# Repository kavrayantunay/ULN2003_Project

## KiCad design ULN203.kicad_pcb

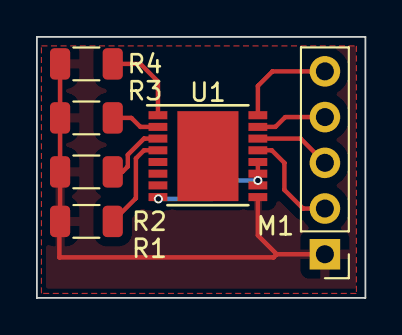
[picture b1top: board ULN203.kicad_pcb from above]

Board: 2 copper layers, 18.2 x 14.5 mm, 6 parts (0 on the bottom side), 10 nets.

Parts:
M1: Stepper_Motor_unipolar_5pin; PinHeader_1x05_P2.54mm_Vertical
R1, R2, R3, R4: 4.7K; R_1206_3216Metric
U1: ULN2003A; HTSSOP-16-1EP_4.4x5mm_P0.65mm_EP3.4x5mm

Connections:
+5V: M1.1, R1.2, R2.2, R3.2, R4.2, U1.9 (COM)
GND: U1.8 (GND), U1.10 (O7), U1.11 (O6), U1.12 (O5)
unnamed: M1.2, U1.13 (O4)
unnamed: M1.3 (-), U1.14 (O3)
unnamed: M1.4, U1.15 (O2)
unnamed: M1.5, U1.16 (O1)
unnamed: R1.1, U1.4 (I4)
unnamed: R2.1, U1.3 (I3)
unnamed: R3.1, U1.2 (I2)
unnamed: R4.1, U1.1 (I1)
